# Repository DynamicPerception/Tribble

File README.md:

Tribble Board
=============

Tribble is the core PCB in the MX3 Motion Controller.

Key Features
------------

 * AT90USB1287 processor with USB OTG
 * 5-Button Interface
 * 2x16 LCD display
 * Dual-optocoupled outputs via 1x TRS jack
 * Four auxiliary I/O ports via 2x TRS jacks
 * MoCoBus Interface
 * Multiple Power Source Inputs

Author
------

The Tribble board was designed and created by Parker Dillmann (longhornengineer)

License and Copyright
---------------------

Tribble and the MX3 are Copyright (c) 2012-2013 Dynamic Perception LLC.

All files shared under the Creative Commons Attibution-Share-Alike 3.0 License.

Tribble and MX3 names are trademarks of Dynamic Perception LLC.

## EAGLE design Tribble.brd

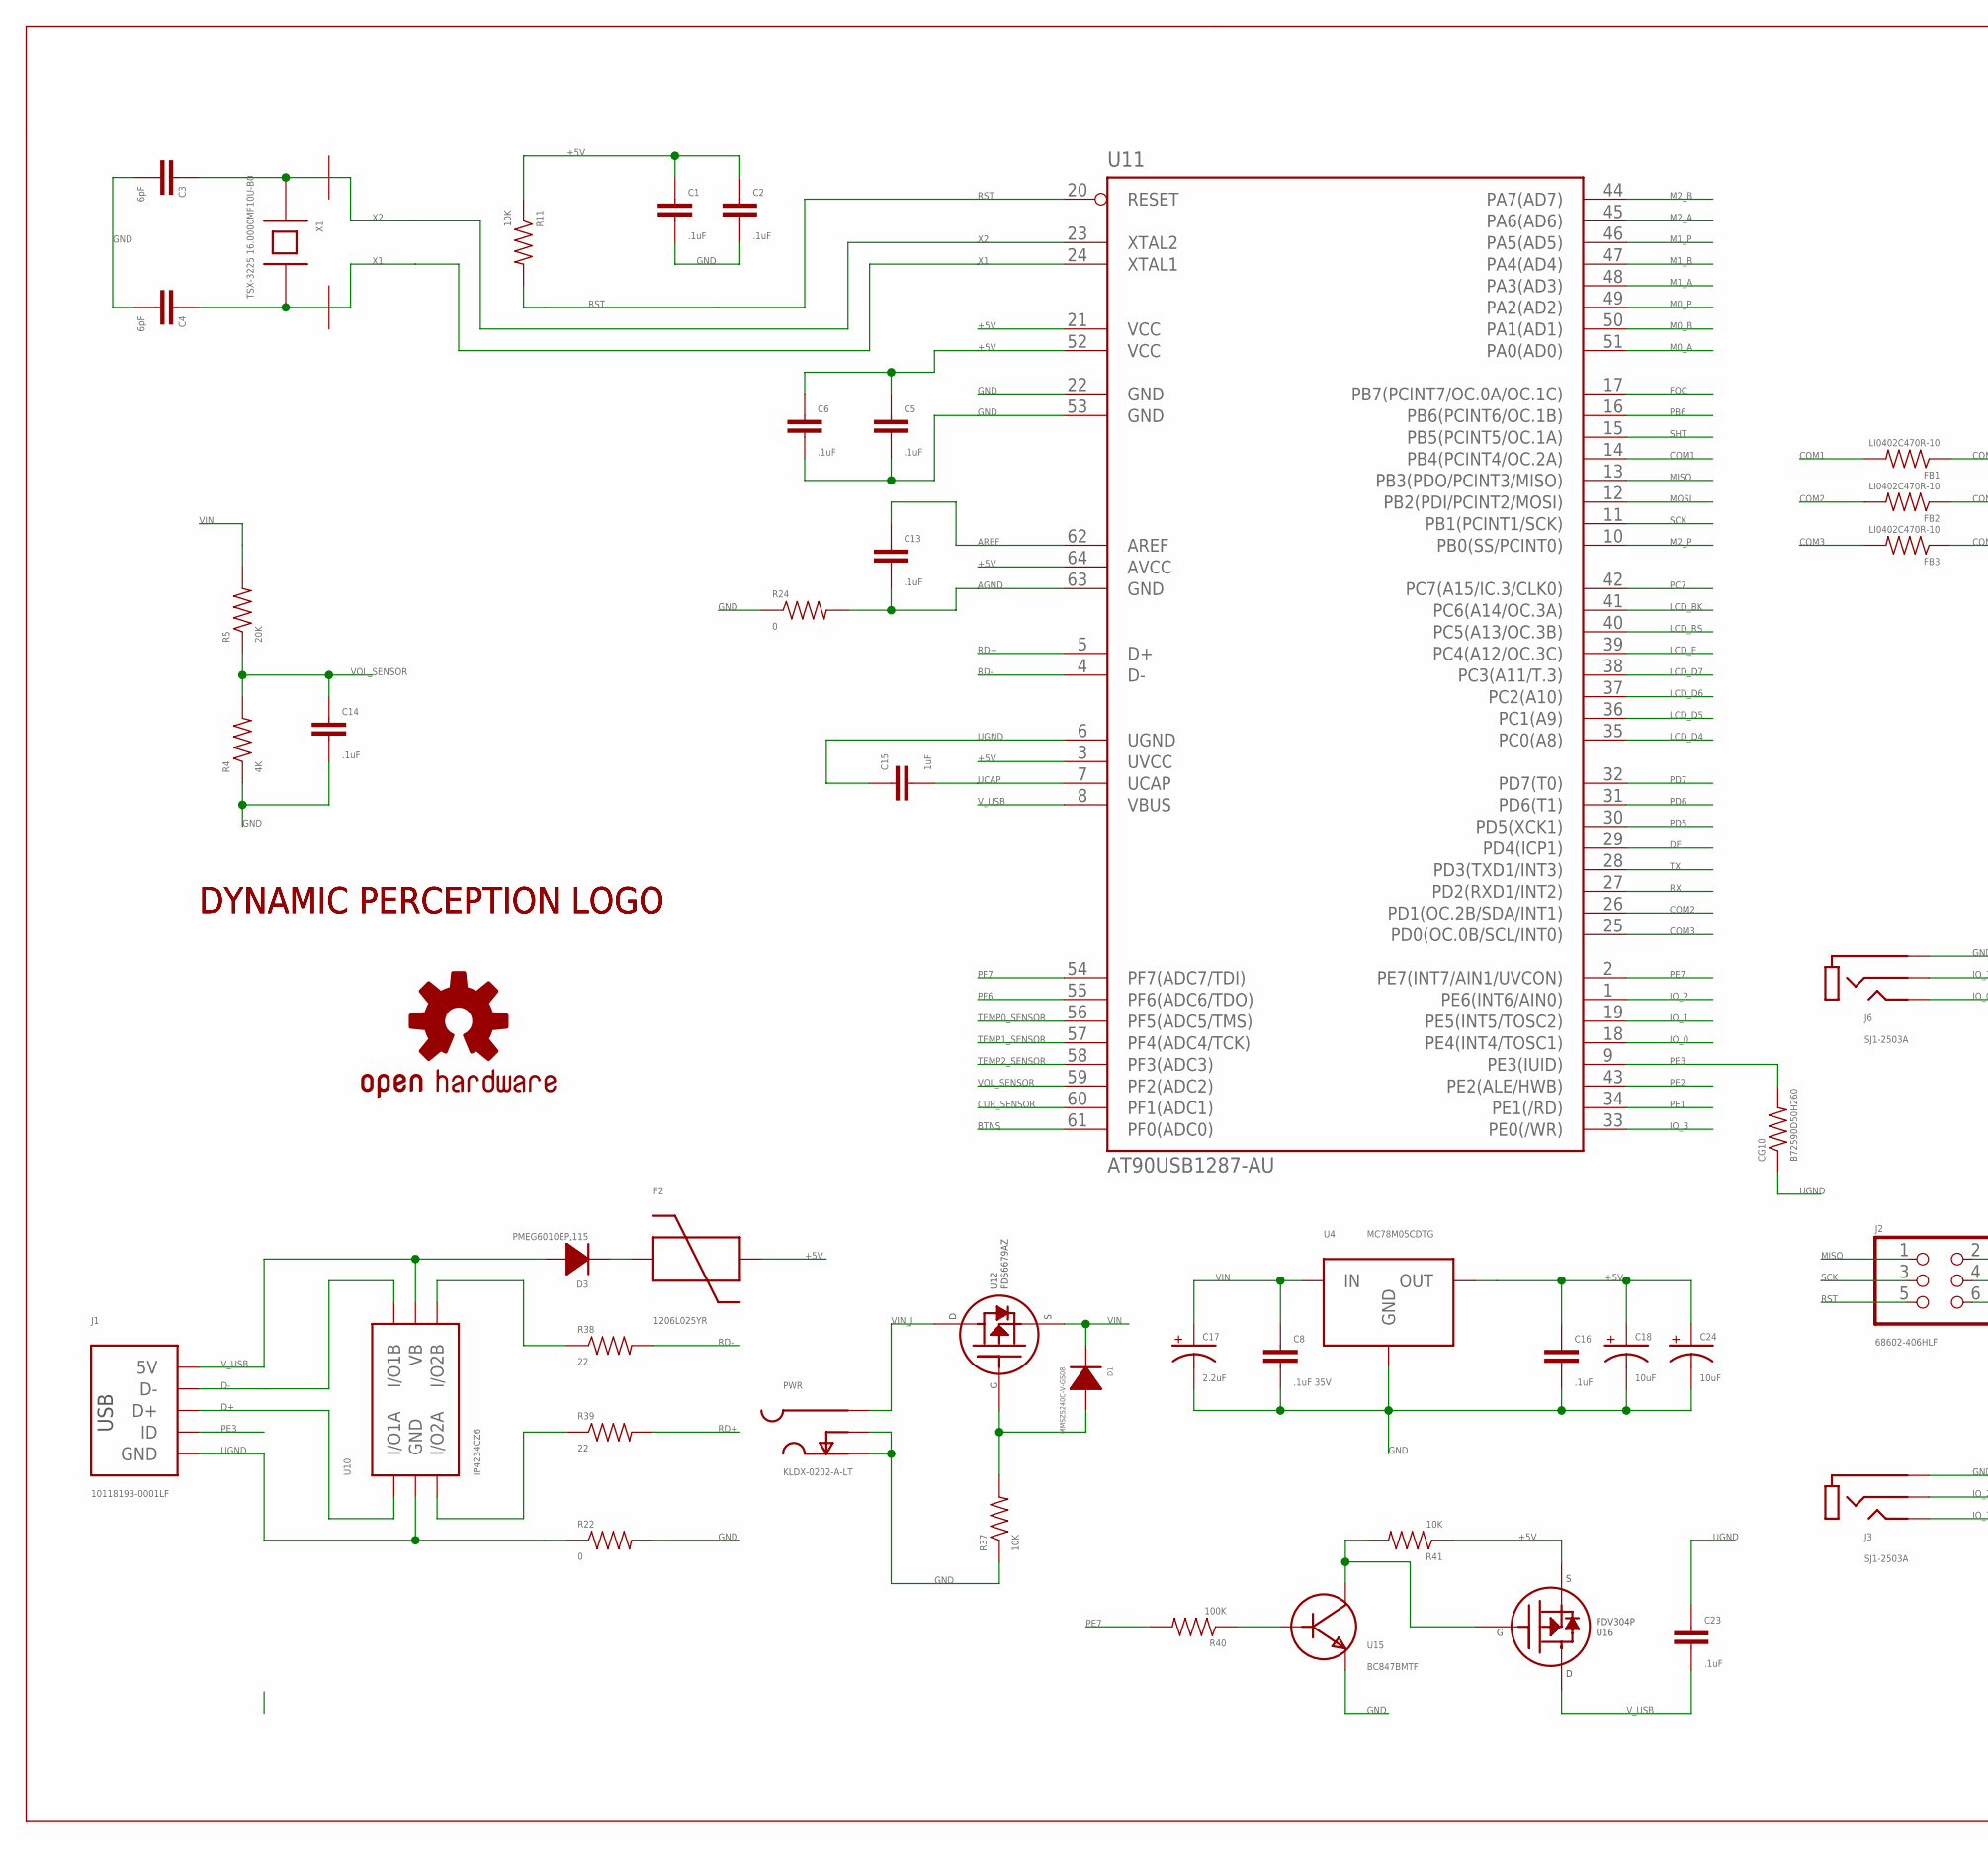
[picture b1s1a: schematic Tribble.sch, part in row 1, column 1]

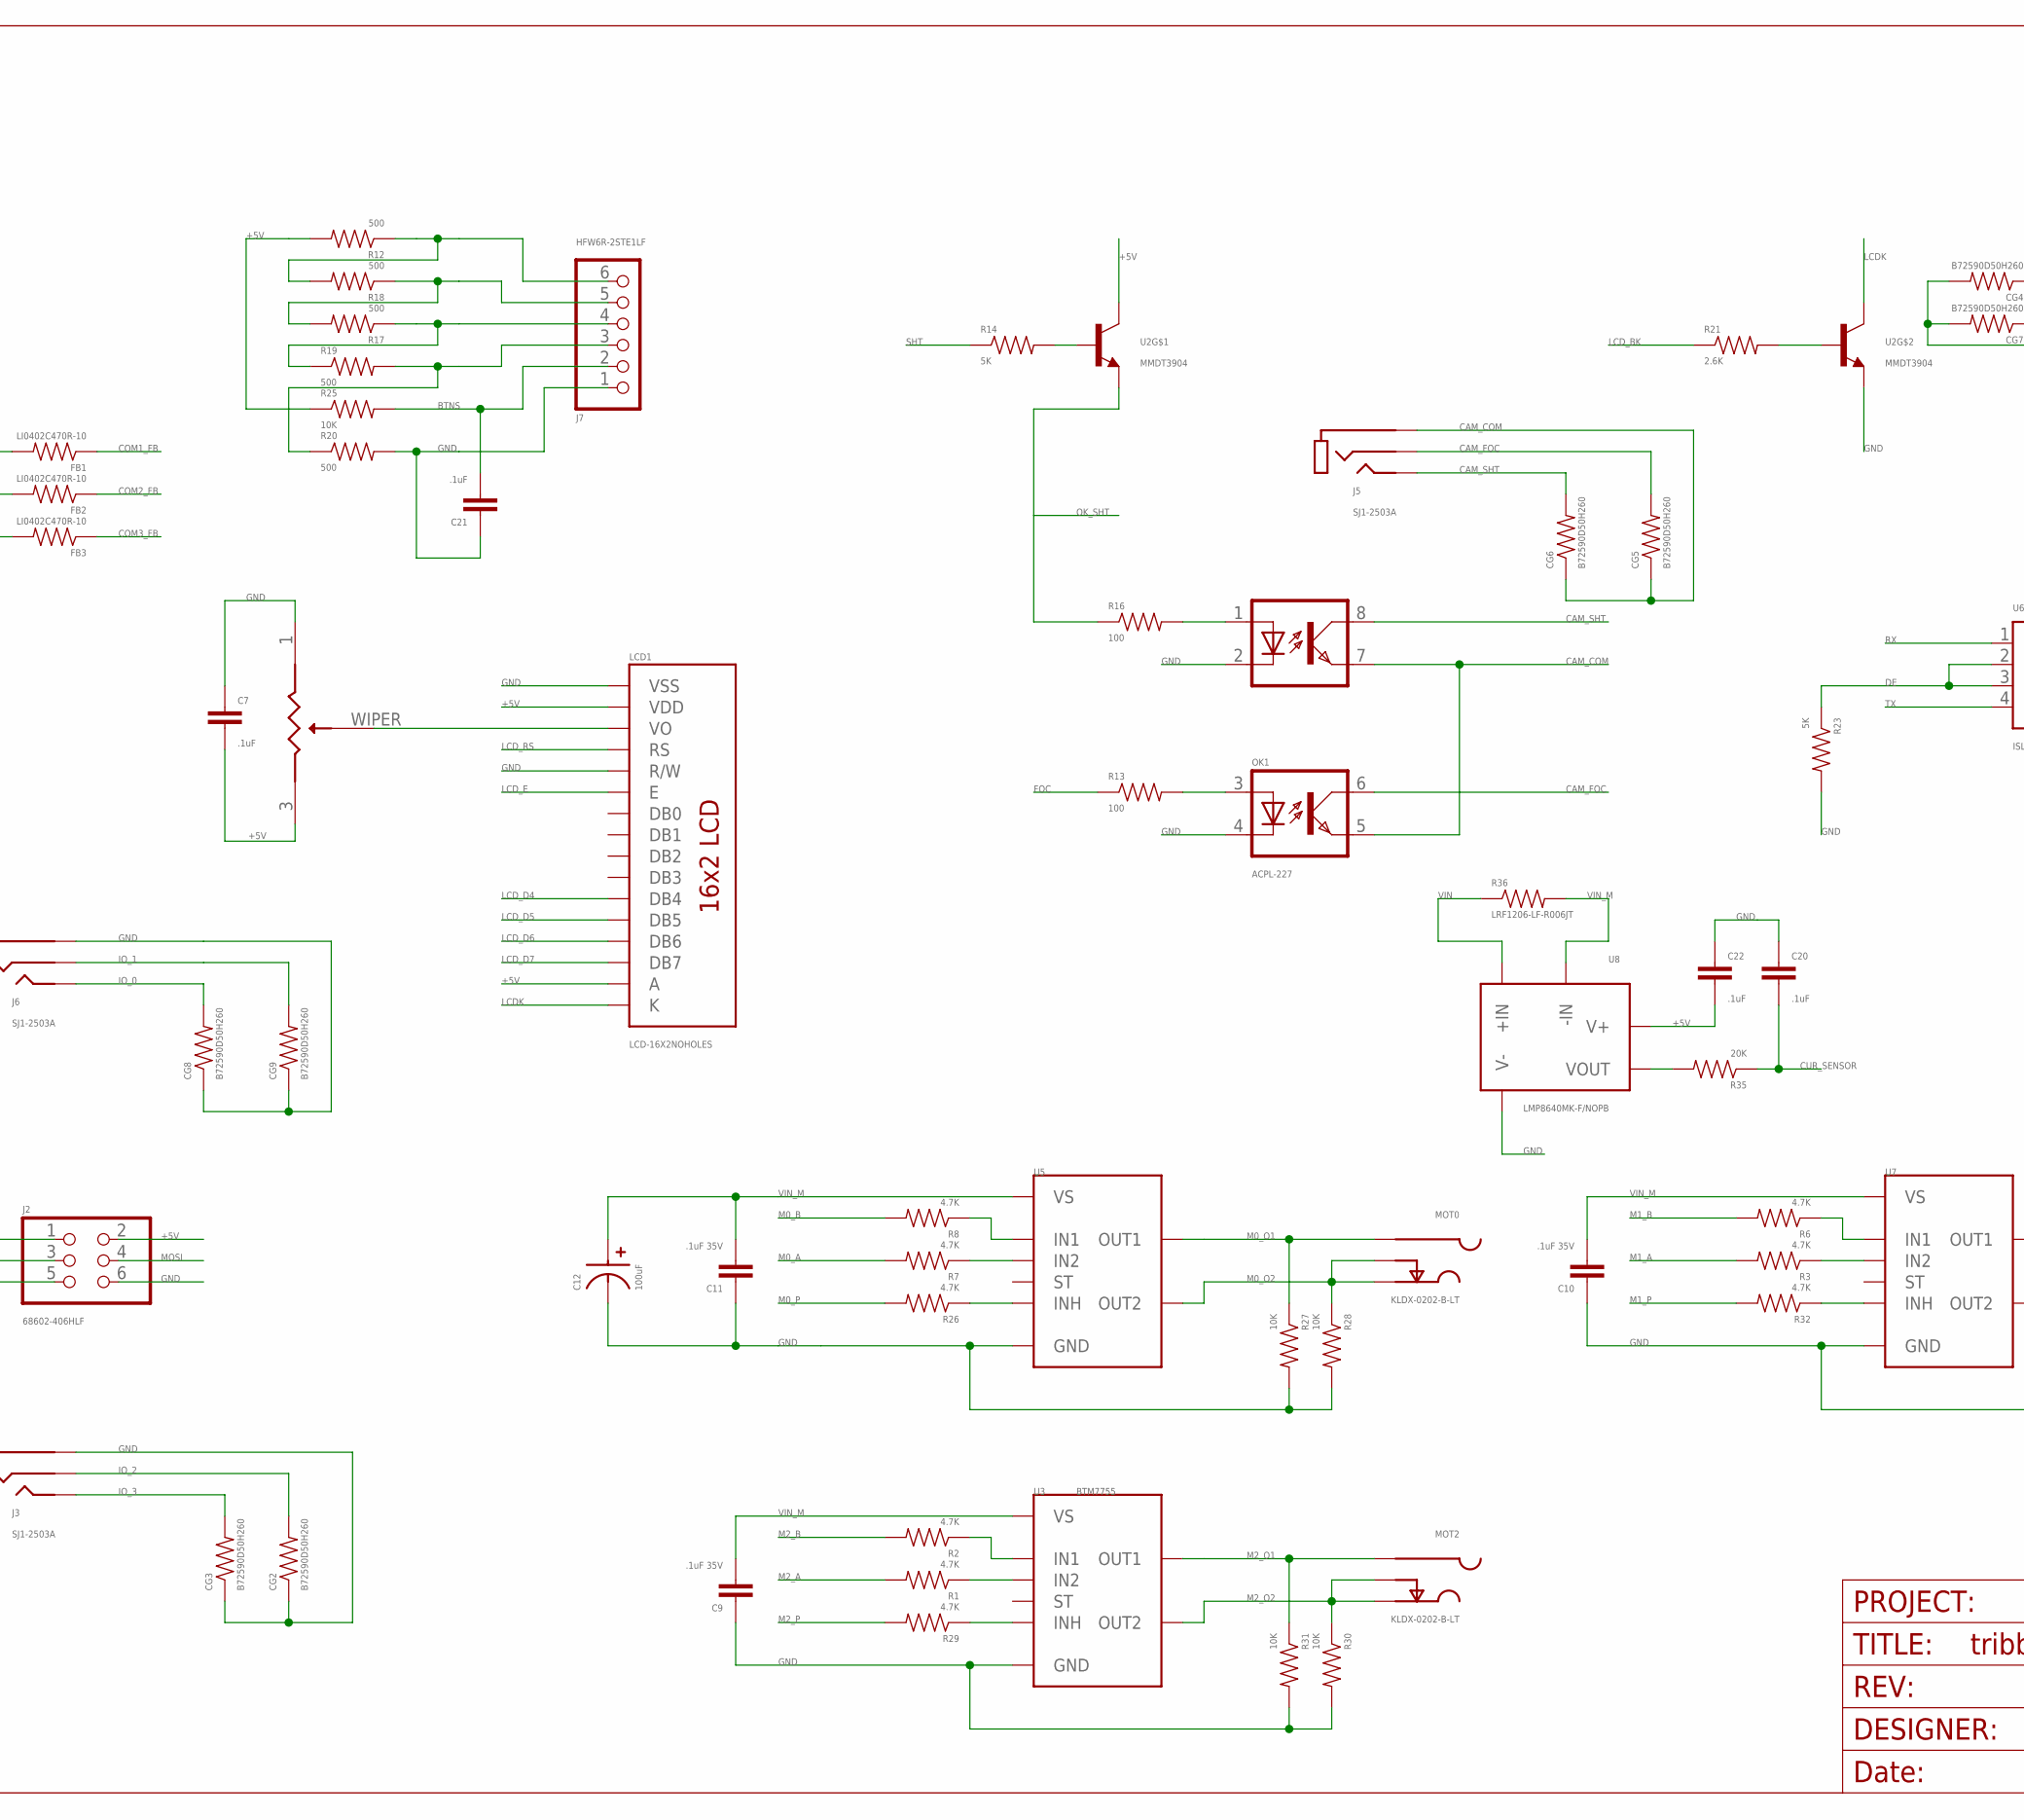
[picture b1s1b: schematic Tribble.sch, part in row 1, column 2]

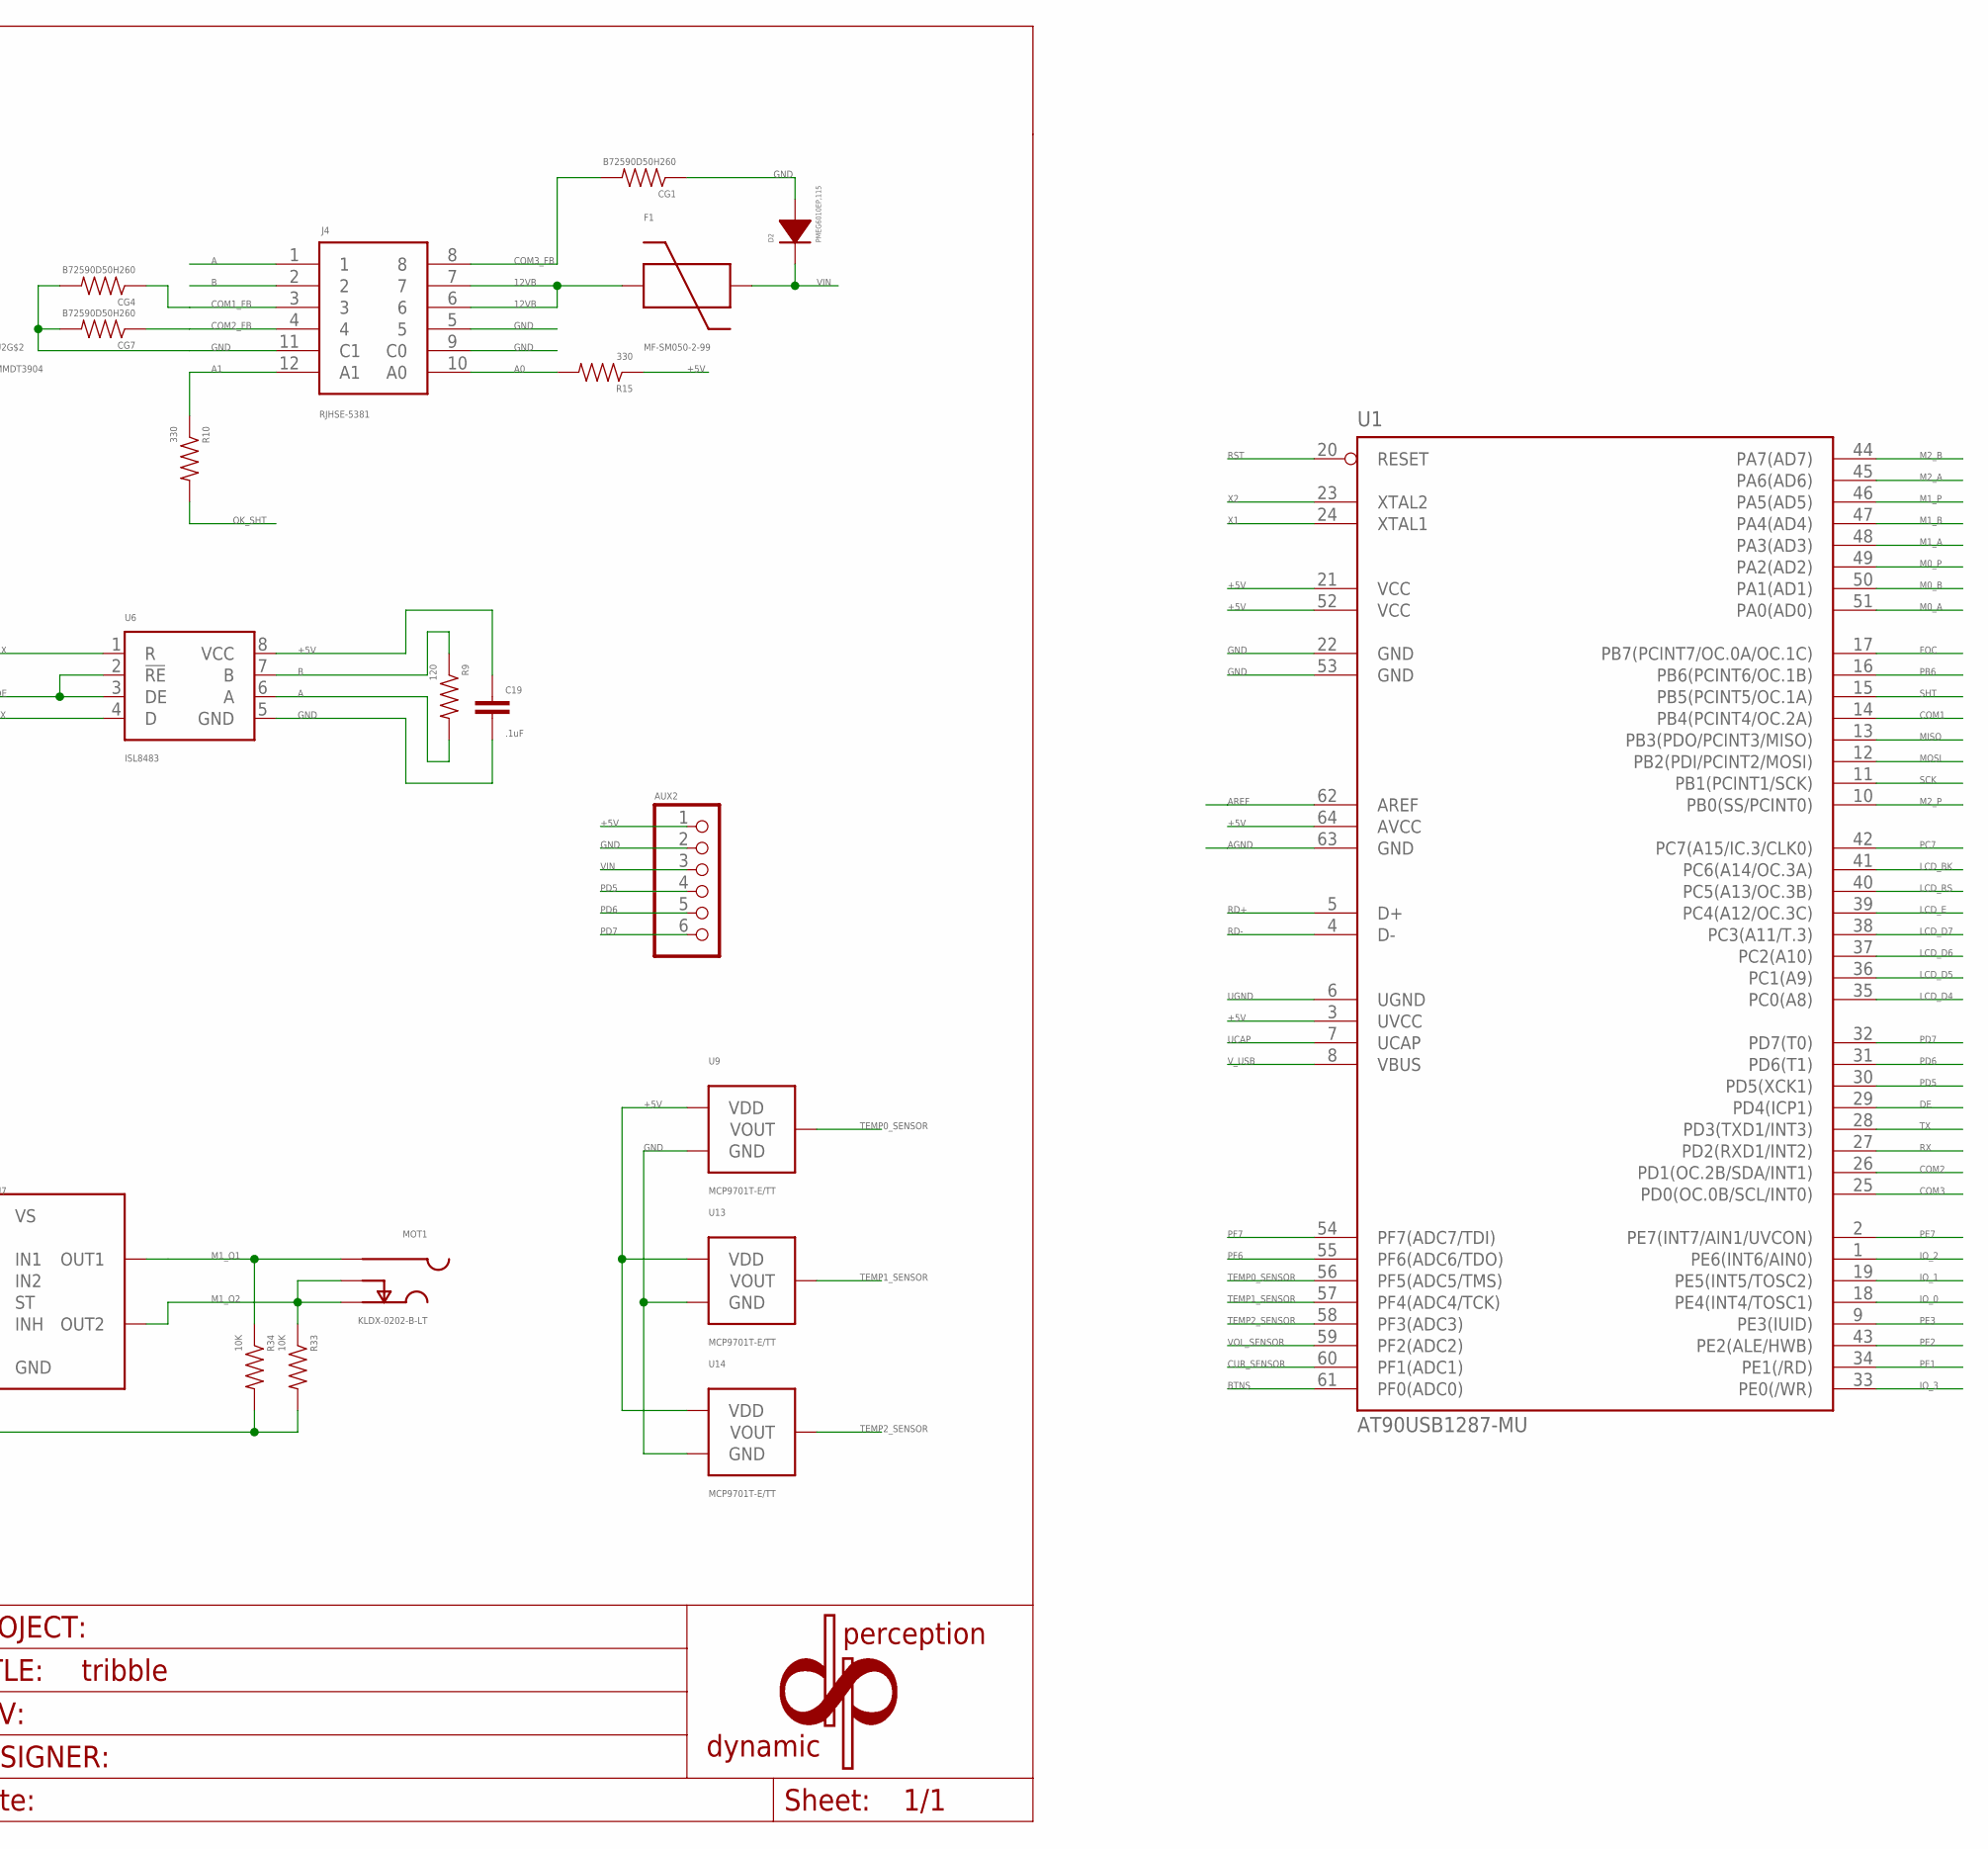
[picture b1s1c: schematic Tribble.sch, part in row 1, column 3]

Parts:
AUX2: PH_1X06SMALL_PTH; HEADER_01X06_SMALL_PTH
C1, C2, C5, C6, C7, C13, C14, C16, C19, C20, C21, C22, C23: .1uF; 0402_CAP
C3, C4: 6pF; C0402
C8, C9, C10, C11: .1uF 35V; 0402_CAP
C12: 100uF; 6.3MM_CAP_SMD
C15: 1uF; 0402_CAP
C17: 2.2uF; EIA3216
C18, C24: 10uF; EIA3216
CG1, CG2, CG3, CG4, CG5, CG6, CG7, CG8, CG9, CG10: B72590D50H260; 0402_RES
D1: MMSZ5240C-V-GS08; SOD-123
D2, D3: PMEG6010EP,115; SOD-128
F1: MF-SM050-2-99; 2920
F2: 1206L025YR; 1206
FB1, FB2, FB3: LI0402C470R-10; 0402_RES
J1: 10118193-0001LF
J2: 68602-406HLF; P2X03
J3, J5, J6: SJ1-2503A
J4: RJHSE-5381; RIGHT_ANGLE
J7: HFW6R-2STE1LF
LCD1: LCD-16X2NOHOLES; LCD-16X2_NOHOLES
LOGO1: DP_LOGOSMALL; DP_LOGO_SMALL
LOGO2: DP_LOGOMICRO; DP_LOGO_MICRO
MOT0, MOT1, MOT2: KLDX-0202-B-LT; DC_JACK_PTH_TIGHT
OK1: ACPL-227; SOIC8
P1: TC33X-2; 3MMSMD
PWR: KLDX-0202-A-LT; DC_JACK_PTH_TIGHT
R1, R2, R3, R6, R7, R8, R26, R29, R32: 4.7K; 0402_RES
R4: 4K; 0402_RES
R5, R35: 20K; 0402_RES
R9: 120; 0402_RES
R10, R15: 330; 0402_RES
R11, R25, R37, R41: 10K; 0402_RES
R12, R17, R18, R19, R20: 500; 0402_RES
R13, R16: 100; 0402_RES
R14, R23: 5K; 0402_RES
R21: 2.6K; 0402_RES
R22, R24: 0; 0402_RES
R27, R28, R30, R31, R33, R34: 10K; 0805
R36: LRF1206-LF-R006JT; 1206
R38, R39: 22; 0402_RES
R40: 100K; 0402_RES
U1: AT90USB1287-MU; MLF64
U2: MMDT3904; SOT363
U3: BTM7755; PG-DSO-36-29
U4: MC78M05CDTG; DPAK-3
U5, U7: BTM7755PG-DSO-36-29; PG-DSO-36-29
U6: ISL8483; SO-08; MPN SN65176BD
U8: LMP8640MK-F/NOPB; TSOT-6
U9, U13, U14: MCP9701T-E/TT; SOT-23-3
U10: IP4234CZ6; SOT-457
U11: AT90USB1287-AU; TQFP64
U12: FDS6679AZ; DSO-8
U15: BC847BMTF; SOT-23
U16: FDV304P; SOT-23
U$1: DP_FRAME
U$2: OSHW-LOGOS; OSHW-LOGO-S
X1: TSX-3225 16.0000MF10U-B0; 3.2X2.5MM

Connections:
4: X1.4
12VB: F1.1, J4.6, J4.7
+5V: AUX2.1, C1.1, C2.1, C5.1, C6.1, C7.2, C16.1, C18.A (+), C19.1, C22.2, C24.A (+), F2.2, J2.2, LCD1.2 (VDD), LCD1.15 (A), P1.3, R11.1, R12.2, R15.1, R25.1, R41.1, U1.3 (UVCC), U1.21 (VCC), U1.52 (VCC), U1.64 (AVCC), U2.3 (C), U4.2 (OUT), U6.8 (VCC), U8.6 (V+), U9.1 (VDD), U11.3 (UVCC), U11.21 (VCC), U11.52 (VCC), U11.64 (AVCC), U13.1 (VDD), U14.1 (VDD), U16.2 (SOURCE)
A: J4.1, R9.2, U6.6 (A)
A0: J4.10 (A0), R15.2
A1: J4.12 (A1), R10.1
AGND: C13.2, R24.2, U1.63 (GND), U11.63 (GND)
AREF: C13.1, U1.62 (AREF), U11.62 (AREF)
B: J4.2, R9.1, U6.7 (B)
BTNS: C21.2, J7.2, R25.2, U1.61 (PF0(ADC0)), U11.61 (PF0(ADC0))
CAM_COM: CG5.1, CG6.1, J5.1 (S), OK1.5 (EMIT1), OK1.7 (EMIT)
CAM_FOC: CG5.2, J5.4 (R), OK1.6 (COL1)
CAM_SHT: CG6.2, J5.2 (T), J5.3 (T), OK1.8 (COL)
COM1: FB1.2, U1.14 (PB4(PCINT4/OC.2A)), U11.14 (PB4(PCINT4/OC.2A))
COM1_FB: CG4.1, FB1.1, J4.3
COM2: FB2.2, U1.26 (PD1(OC.2B/SDA/INT1)), U11.26 (PD1(OC.2B/SDA/INT1))
COM2_FB: CG7.1, FB2.1, J4.4
COM3: FB3.2, U1.25 (PD0(OC.0B/SCL/INT0)), U11.25 (PD0(OC.0B/SCL/INT0))
COM3_FB: CG1.2, FB3.1, J4.8
CUR_SENSOR: C20.2, R35.1, U1.60 (PF1(ADC1)), U11.60 (PF1(ADC1))
D+: J1.3 (D+), U10.1 (I/O1A)
D-: J1.2 (D-), U10.6 (I/O1B)
DE: R23.1, U1.29 (PD4(ICP1)), U6.2 (!RE), U6.3 (DE), U11.29 (PD4(ICP1))
FDV_GATE: R41.2, U15.3 (COLLECTOR), U16.1 (GATE)
FOC: R13.1, U1.17 (PB7(PCINT7/OC.0A/OC.1C)), U11.17 (PB7(PCINT7/OC.0A/OC.1C))
GND: AUX2.2, C1.2, C2.2, C3.1, C4.1, C5.2, C6.2, C7.1, C8.2, C9.1, C10.1, C11.1, C12.NEG, C14.2, C16.2, C17.C (-), C18.C (-), C19.2, C20.1, C21.1, C22.1, C24.C (-), CG1.1, CG2.1, CG3.1, CG4.2, CG7.2, CG8.1, CG9.1, D2.ANODE, J2.6, J3.1 (S), J4.5, J4.9 (C0), J4.11 (C1), J6.1 (S), J7.1, LCD1.1 (VSS), LCD1.5 (R/W), OK1.2 (C), OK1.4 (C1), P1.1, PWR.GND (SLEEVE), PWR.GNDBREAK (SLEEVE_SHUNT), R4.1, R20.2, R22.2, R23.2, R24.1, R27.2, R28.2, R30.2, R31.2, R33.2, R34.2, R37.1, U1.22 (GND), U1.53 (GND), U2.1 (E), U3.5 (GND), U3.6 (GND), U3.7 (GND), U3.8 (GND), U3.23 (GND), U3.24 (GND), U3.25 (GND), U3.26 (GND), U4.4 (GND), U5.5 (GND), U5.6 (GND), U5.7 (GND), U5.8 (GND), U5.23 (GND), U5.24 (GND), U5.25 (GND), U5.26 (GND), U6.5 (GND), U7.5 (GND), U7.6 (GND), U7.7 (GND), U7.8 (GND), U7.23 (GND), U7.24 (GND), U7.25 (GND), U7.26 (GND), U8.2 (V-), U9.3 (GND), U11.22 (GND), U11.53 (GND), U13.3 (GND), U14.3 (GND), U15.2 (EMITTER), X1.2 (GND)
IO_0: CG8.2, J6.2 (T), J6.3 (T), U1.18 (PE4(INT4/TOSC1)), U11.18 (PE4(INT4/TOSC1))
IO_1: CG9.2, J6.4 (R), U1.19 (PE5(INT5/TOSC2)), U11.19 (PE5(INT5/TOSC2))
IO_2: CG2.2, J3.4 (R), U1.1 (PE6(INT6/AIN0)), U11.1 (PE6(INT6/AIN0))
IO_3: CG3.2, J3.2 (T), J3.3 (T), U1.33 (PE0(/WR)), U11.33 (PE0(/WR))
LCDK: LCD1.16 (K), U2.6 (C)
LCD_BK: R21.1, U1.41 (PC6(A14/OC.3A)), U11.41 (PC6(A14/OC.3A))
LCD_D4: LCD1.11 (DB4), U1.35 (PC0(A8)), U11.35 (PC0(A8))
LCD_D5: LCD1.12 (DB5), U1.36 (PC1(A9)), U11.36 (PC1(A9))
LCD_D6: LCD1.13 (DB6), U1.37 (PC2(A10)), U11.37 (PC2(A10))
LCD_D7: LCD1.14 (DB7), U1.38 (PC3(A11/T.3)), U11.38 (PC3(A11/T.3))
LCD_E: LCD1.6 (E), U1.39 (PC4(A12/OC.3C)), U11.39 (PC4(A12/OC.3C))
LCD_RS: LCD1.4 (RS), U1.40 (PC5(A13/OC.3B)), U11.40 (PC5(A13/OC.3B))
M0_A: R7.2, U1.51 (PA0(AD0)), U11.51 (PA0(AD0))
M0_A1: R7.1, U5.10 (IN2)
M0_B: R8.2, U1.50 (PA1(AD1)), U11.50 (PA1(AD1))
M0_B1: R8.1, U5.9 (IN1)
M0_O1: MOT0.PWR (PIN), R27.1, U5.1 (OUT1), U5.2 (OUT1), U5.3 (OUT1), U5.4 (OUT1), U5.33 (OUT1), U5.34 (OUT1), U5.35 (OUT1), U5.36 (OUT1)
M0_O2: MOT0.GND (SLEEVE), MOT0.GNDBREAK (SLEEVE_SHUNT), R28.1, U5.15 (OUT2), U5.16 (OUT2), U5.17 (OUT2), U5.18 (OUT2), U5.19 (OUT2), U5.20 (OUT2), U5.21 (OUT2), U5.22 (OUT2)
M0_P: R26.2, U1.49 (PA2(AD2)), U11.49 (PA2(AD2))
M0_P1: R26.1, U5.27 (INH)
M1_A: R3.2, U1.48 (PA3(AD3)), U11.48 (PA3(AD3))
M1_B: R6.2, U1.47 (PA4(AD4)), U11.47 (PA4(AD4))
M1_O1: MOT1.PWR (PIN), R34.1, U7.1 (OUT1), U7.2 (OUT1), U7.3 (OUT1), U7.4 (OUT1), U7.33 (OUT1), U7.34 (OUT1), U7.35 (OUT1), U7.36 (OUT1)
M1_O2: MOT1.GND (SLEEVE), MOT1.GNDBREAK (SLEEVE_SHUNT), R33.1, U7.15 (OUT2), U7.16 (OUT2), U7.17 (OUT2), U7.18 (OUT2), U7.19 (OUT2), U7.20 (OUT2), U7.21 (OUT2), U7.22 (OUT2)
M1_P: R32.2, U1.46 (PA5(AD5)), U11.46 (PA5(AD5))
M2_A: R1.2, U1.45 (PA6(AD6)), U11.45 (PA6(AD6))
M2_B: R2.2, U1.44 (PA7(AD7)), U11.44 (PA7(AD7))
M2_O1: MOT2.PWR (PIN), R31.1, U3.1 (OUT1), U3.2 (OUT1), U3.3 (OUT1), U3.4 (OUT1), U3.33 (OUT1), U3.34 (OUT1), U3.35 (OUT1), U3.36 (OUT1)
M2_O2: MOT2.GND (SLEEVE), MOT2.GNDBREAK (SLEEVE_SHUNT), R30.1, U3.15 (OUT2), U3.16 (OUT2), U3.17 (OUT2), U3.18 (OUT2), U3.19 (OUT2), U3.20 (OUT2), U3.21 (OUT2), U3.22 (OUT2)
M2_P: R29.2, U1.10 (PB0(SS/PCINT0)), U11.10 (PB0(SS/PCINT0))
MISO: J2.1, U1.13 (PB3(PDO/PCINT3/MISO)), U11.13 (PB3(PDO/PCINT3/MISO))
MOSI: J2.4, U1.12 (PB2(PDI/PCINT2/MOSI)), U11.12 (PB2(PDI/PCINT2/MOSI))
unnamed: R35.2, U8.1 (VOUT)
unnamed: D1.ANODE, R37.2, U12.4 (GATE)
unnamed: R3.1, U7.10 (IN2)
unnamed: R21.2, U2.2 (B)
unnamed: R6.1, U7.9 (IN1)
unnamed: R32.1, U7.27 (INH)
unnamed: R29.1, U3.27 (INH)
unnamed: R2.1, U3.9 (IN1)
unnamed: R1.1, U3.10 (IN2)
unnamed: R38.1, U10.4 (I/O2B)
unnamed: R39.1, U10.3 (I/O2A)
unnamed: D3.CATHODE, F2.1
unnamed: LCD1.3 (VO), P1.WIPER (2)
unnamed: OK1.3 (A1), R13.2
unnamed: OK1.1 (A), R16.2
unnamed: R14.2, U2.5 (B)
unnamed: J7.6, R12.1, R18.2
unnamed: J7.4, R17.1, R19.1
unnamed: J7.5, R17.2, R18.1
unnamed: J7.3, R19.2, R20.1
OK_SHT: R10.2, R16.1, U2.4 (E)
PB6: U1.16 (PB6(PCINT6/OC.1B)), U11.16 (PB6(PCINT6/OC.1B))
PC7: U1.42 (PC7(A15/IC.3/CLK0)), U11.42 (PC7(A15/IC.3/CLK0))
PD5: AUX2.4, U1.30 (PD5(XCK1)), U11.30 (PD5(XCK1))
PD6: AUX2.5, U1.31 (PD6(T1)), U11.31 (PD6(T1))
PD7: AUX2.6, U1.32 (PD7(T0)), U11.32 (PD7(T0))
PE1: U1.34 (PE1(/RD)), U11.34 (PE1(/RD))
PE2: U1.43 (PE2(ALE/HWB)), U11.43 (PE2(ALE/HWB))
PE3: CG10.2, J1.4 (ID), U1.9 (PE3(IUID)), U11.9 (PE3(IUID))
PE7: R40.2, U1.2 (PE7(INT7/AIN1/UVCON)), U11.2 (PE7(INT7/AIN1/UVCON))
PE7_GATE: R40.1, U15.1 (BASE)
PF6: U1.55 (PF6(ADC6/TDO)), U11.55 (PF6(ADC6/TDO))
PF7: U1.54 (PF7(ADC7/TDI)), U11.54 (PF7(ADC7/TDI))
RD+: R39.2, U1.5 (D+), U11.5 (D+)
RD-: R38.2, U1.4 (D-), U11.4 (D-)
RST: J2.5, R11.2, U1.20 (RESET), U11.20 (RESET)
RX: U1.27 (PD2(RXD1/INT2)), U6.1 (R), U11.27 (PD2(RXD1/INT2))
SCK: J2.3, U1.11 (PB1(PCINT1/SCK)), U11.11 (PB1(PCINT1/SCK))
SHT: R14.1, U1.15 (PB5(PCINT5/OC.1A)), U11.15 (PB5(PCINT5/OC.1A))
TEMP0_SENSOR: U1.56 (PF5(ADC5/TMS)), U9.2 (VOUT), U11.56 (PF5(ADC5/TMS))
TEMP1_SENSOR: U1.57 (PF4(ADC4/TCK)), U11.57 (PF4(ADC4/TCK)), U13.2 (VOUT)
TEMP2_SENSOR: U1.58 (PF3(ADC3)), U11.58 (PF3(ADC3)), U14.2 (VOUT)
TX: U1.28 (PD3(TXD1/INT3)), U6.4 (D), U11.28 (PD3(TXD1/INT3))
UCAP: C15.2, U1.7 (UCAP), U11.7 (UCAP)
UGND: C15.1, C23.1, CG10.1, J1.5 (GND), J1.S1 (GND), J1.S2 (GND), J1.S3 (GND), J1.S4 (GND), R22.1, U1.6 (UGND), U10.2 (GND), U11.6 (UGND)
VIN: AUX2.3, C8.1, C17.A (+), D1.CATHODE, D2.CATHODE, F1.2, R5.2, R36.1, U4.1 (IN), U8.3 (+IN), U12.1 (SOURCE), U12.2 (SOURCE), U12.3 (SOURCE)
VIN_J: PWR.PWR (PIN), U12.5 (DRAIN), U12.6 (DRAIN), U12.7 (DRAIN), U12.8 (DRAIN)
VIN_M: C9.2, C10.2, C11.2, C12.POS, R36.2, U3.11 (VS), U3.12 (VS), U3.13 (VS), U3.14 (VS), U3.29 (VS), U3.30 (VS), U3.31 (VS), U3.32 (VS), U5.11 (VS), U5.12 (VS), U5.13 (VS), U5.14 (VS), U5.29 (VS), U5.30 (VS), U5.31 (VS), U5.32 (VS), U7.11 (VS), U7.12 (VS), U7.13 (VS), U7.14 (VS), U7.29 (VS), U7.30 (VS), U7.31 (VS), U7.32 (VS), U8.4 (-IN)
VOL_SENSOR: C14.1, R4.2, R5.1, U1.59 (PF2(ADC2)), U11.59 (PF2(ADC2))
V_USB: C23.2, D3.ANODE, J1.1 (5V), U1.8 (VBUS), U10.5 (VB), U11.8 (VBUS), U16.3 (DRAIN)
X1: C4.2, U1.24 (XTAL1), U11.24 (XTAL1), X1.3
X2: C3.2, U1.23 (XTAL2), U11.23 (XTAL2), X1.1

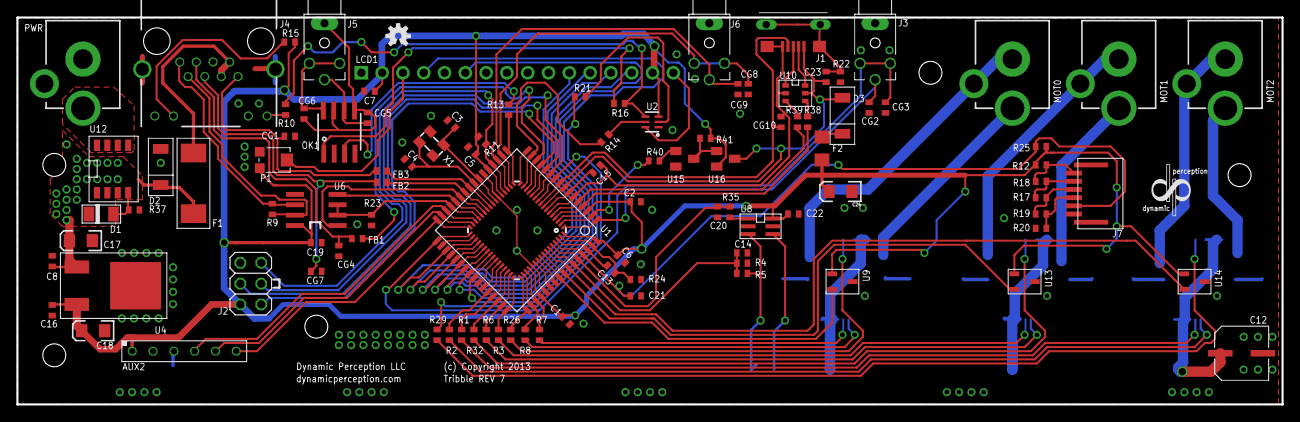
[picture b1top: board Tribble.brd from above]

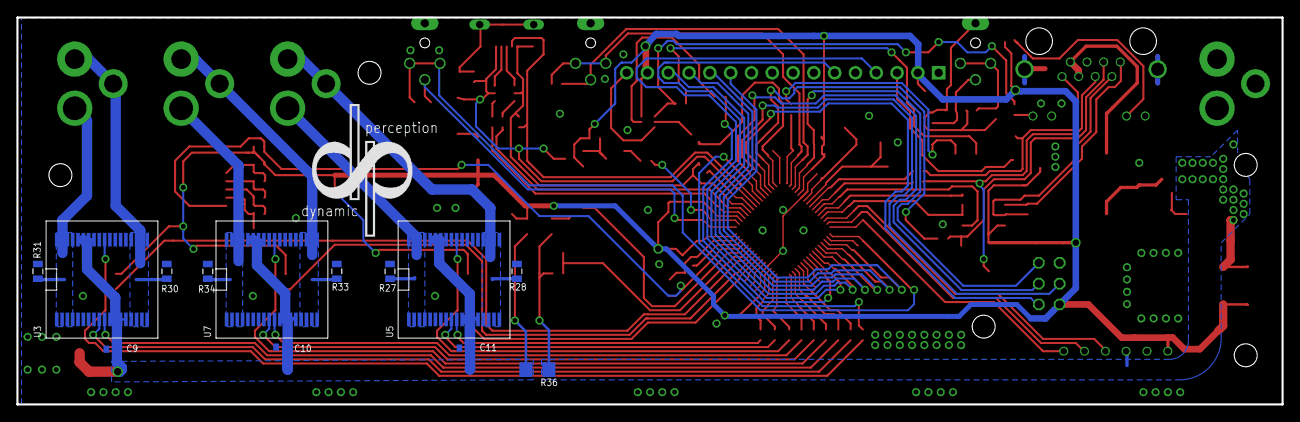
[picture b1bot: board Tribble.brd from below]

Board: 2 copper layers, 154.5 x 47.2 mm, 119 parts (14 on the bottom side), 109 nets.

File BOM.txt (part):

Partlist

Exported from Tribble.sch at 5/22/2013 1:43:17 PM

EAGLE Version 6.2.0 Copyright (c) 1988-2012 CadSoft

Assembly variant: 

Part     Value                    Device                          Package                Library               Sheet

AUX2                              PH_1X06SMALL_PTH                HEADER_01X06_SMALL_PTH PP_Connectors         1
C1       .1uF                     CAP_NONPOL0402                  0402_CAP               parkers_parts         1
C2       .1uF                     CAP_NONPOL0402                  0402_CAP               parkers_parts         1
C3       6pF                      CAP0402                         C0402                  SparkFun              1
C4       6pF                      CAP0402                         C0402                  SparkFun              1
C5       .1uF                     CAP_NONPOL0402                  0402_CAP               parkers_parts         1
C6       .1uF                     CAP_NONPOL0402                  0402_CAP               parkers_parts         1
C7       .1uF                     CAP_NONPOL0402                  0402_CAP               parkers_parts         1
C8       .1uF 35V                 CAP_NONPOL0402                  0402_CAP               parkers_parts         1
C9       .1uF 35V                 CAP_NONPOL0402                  0402_CAP               parkers_parts         1
C10      .1uF 35V                 CAP_NONPOL0402                  0402_CAP               parkers_parts         1
C11      .1uF 35V                 CAP_NONPOL0402                  0402_CAP               parkers_parts         1
C12      100uF                    CAPACITOR_POLARIZED6.3MM_SMD    6.3MM_CAP_SMD          PP_Passives           1
C13      .1uF                     CAP_NONPOL0402                  0402_CAP               parkers_parts         1
C14      .1uF                     CAP_NONPOL0402                  0402_CAP               parkers_parts         1
C15      1uF                      CAP_NONPOL0402                  0402_CAP               parkers_parts         1
C16      .1uF                     CAP_NONPOL0402                  0402_CAP               parkers_parts         1
C17      2.2uF                    CAP_POL1206                     EIA3216                SparkFun              1
C18      10uF                     CAP_POL1206                     EIA3216                SparkFun              1
C19      .1uF                     CAP_NONPOL0402                  0402_CAP               parkers_parts         1
C20      .1uF                     CAP_NONPOL0402                  0402_CAP               parkers_parts         1
C21      .1uF                     CAP_NONPOL0402                  0402_CAP               parkers_parts         1
C22      .1uF                     CAP_NONPOL0402                  0402_CAP               parkers_parts         1
C23      .1uF                     CAP_NONPOL0402                  0402_CAP               parkers_parts         1
C24      10uF                     CAP_POL1206                     EIA3216                SparkFun              1
CG1      B72590D50H260            RESISTOR0402                    0402_RES               parkers_parts         1
CG2      B72590D50H260            RESISTOR0402                    0402_RES               parkers_parts         1
CG3      B72590D50H260            RESISTOR0402                    0402_RES               parkers_parts         1
CG4      B72590D50H260            RESISTOR0402                    0402_RES               parkers_parts         1
CG5      B72590D50H260            RESISTOR0402                    0402_RES               parkers_parts         1
CG6      B72590D50H260            RESISTOR0402                    0402_RES               parkers_parts         1
CG7      B72590D50H260            RESISTOR0402                    0402_RES               parkers_parts         1
CG8      B72590D50H260            RESISTOR0402                    0402_RES               parkers_parts         1
CG9      B72590D50H260            RESISTOR0402                    0402_RES               parkers_parts         1
CG10     B72590D50H260            RESISTOR0402                    0402_RES               parkers_parts         1
D1       MMSZ5240C-V-GS08         DIODESOD-123                    SOD-123                parkers_parts         1
D2       PMEG6010EP,115           DIODESOD-128                    SOD-128                parkers_parts         1
D3       PMEG6010EP,115           DIODESOD-128                    SOD-128                PP_Passives           1
F1       MF-SM050-2-99            PTC_FUSE2920                    2920                   PP_Passives           1
F2       1206L025YR               PTC_FUSE1206                    1206                   PP_Passives           1
FB1      LI0402C470R-10           RESISTOR0402                    0402_RES               parkers_parts         1
FB2      LI0402C470R-10           RESISTOR0402                    0402_RES               parkers_parts         1
FB3      LI0402C470R-10           RESISTOR0402                    0402_RES               parkers_parts         1
J1       10118193-0001LF          USB10118193-0001LF              10118193-0001LF        PP_Connectors         1
J2       68602-406HLF             P2X03                           P2X03                  parkers_parts         1
J3       SJ1-2503A                TRS_STEREO_JACKSJ1-2503A        SJ1-2503A              parkers_parts         1
J4       RJHSE-5381               RJHS-538X                       RIGHT_ANGLE            amphenol ethernet     1
J5       SJ1-2503A                TRS_STEREO_JACKSJ1-2503A        SJ1-2503A              parkers_parts         1
J6       SJ1-2503A                TRS_STEREO_JACKSJ1-2503A        SJ1-2503A              parkers_parts         1
J7       HFW6R-2STE1LF            PH_1X06FFC                      HFW6R-2STE1LF          PP_Connectors         1
LCD1     LCD-16X2NOHOLES          LCD-16X2NOHOLES                 LCD-16X2_NOHOLES       SparkFun-Displays     1
MOT0     KLDX-0202-B-LT           DC_JACKPTH_TIGHT                DC_JACK_PTH_TIGHT      PP_Connectors         1
MOT1     KLDX-0202-B-LT           DC_JACKPTH_TIGHT                DC_JACK_PTH_TIGHT      PP_Connectors         1
MOT2     KLDX-0202-B-LT           DC_JACKPTH_TIGHT                DC_JACK_PTH_TIGHT      PP_Connectors         1
OK1      ACPL-227                 ACPL-227                        SOIC8                  avago-opto            1
P1       TC33X-2                  TC33X-2                         3MMSMD                 bourns trimpot        1
PWR      KLDX-0202-A-LT           DC_JACKPTH_TIGHT                DC_JACK_PTH_TIGHT      PP_Connectors         1
R1       4.7K                     RESISTOR0402                    0402_RES               parkers_parts         1
R2       4.7K                     RESISTOR0402                    0402_RES               parkers_parts         1
R3       4.7K                     RESISTOR0402                    0402_RES               parkers_parts         1
R4       4K                       RESISTOR0402                    0402_RES               parkers_parts         1
R5       20K                      RESISTOR0402                    0402_RES               parkers_parts         1
R6       4.7K                     RESISTOR0402                    0402_RES               parkers_parts         1
R7       4.7K                     RESISTOR0402                    0402_RES               parkers_parts         1
R8       4.7K                     RESISTOR0402                    0402_RES               parkers_parts         1
R9       120                      RESISTOR0402                    0402_RES               parkers_parts         1
R10      330                      RESISTOR0402                    0402_RES               parkers_parts         1
R11      10K                      RESISTOR0402                    0402_RES               parkers_parts         1
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

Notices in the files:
Tribble.brd:
(c) Copyright 2013
parts and their libraries:
PP_Aesthetics: (c) 2012 Dynamic Perception LLC
SparkFun-DiscreteSemi: Licensing: CC v3.0 Share-Alike You are welcome to use this library for commercial purposes.
